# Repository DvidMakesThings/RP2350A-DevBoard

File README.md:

# RP2350A-DevBoard Project

## Contents
This folder contains all the documents related to the RP2350A-DevBoard project.

## Usage
To use the files in this project, navigate to the respective directories and follow the instructions provided in each document.

## License
This project is licensed under the MIT License.

## Contact
For any questions or feedback, please contact:
- Email: [s.dvid@hotmail.com](mailto:s.dvid@hotmail.com)
- GitHub: [DvidMakesThings](https://github.com/DvidMakesThings)

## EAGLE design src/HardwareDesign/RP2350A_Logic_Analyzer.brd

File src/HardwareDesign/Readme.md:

# # RP2350A-DevBoard Project Hardware Design Files

## Contents
This folder contains the hardware design files for the RP2350A-DevBoard project. The main components include:
- Schematic diagrams
- PCB layouts
- Bill of Materials (BOM)
- Gerber files

## Usage
To use these hardware design files:
1. Open the schematic diagrams and PCB layouts using EAGLE software.
2. Review the Bill of Materials for required components.
3. Follow the design files to assemble and test the hardware.
4. Use the Gerber files for PCB manufacturing.

## License
This project is licensed under the MIT License.

## Contact
For any questions or feedback, please contact:
- Email: [s.dvid@hotmail.com](mailto:s.dvid@hotmail.com)
- GitHub: [DvidMakesThings](https://github.com/DvidMakesThings)

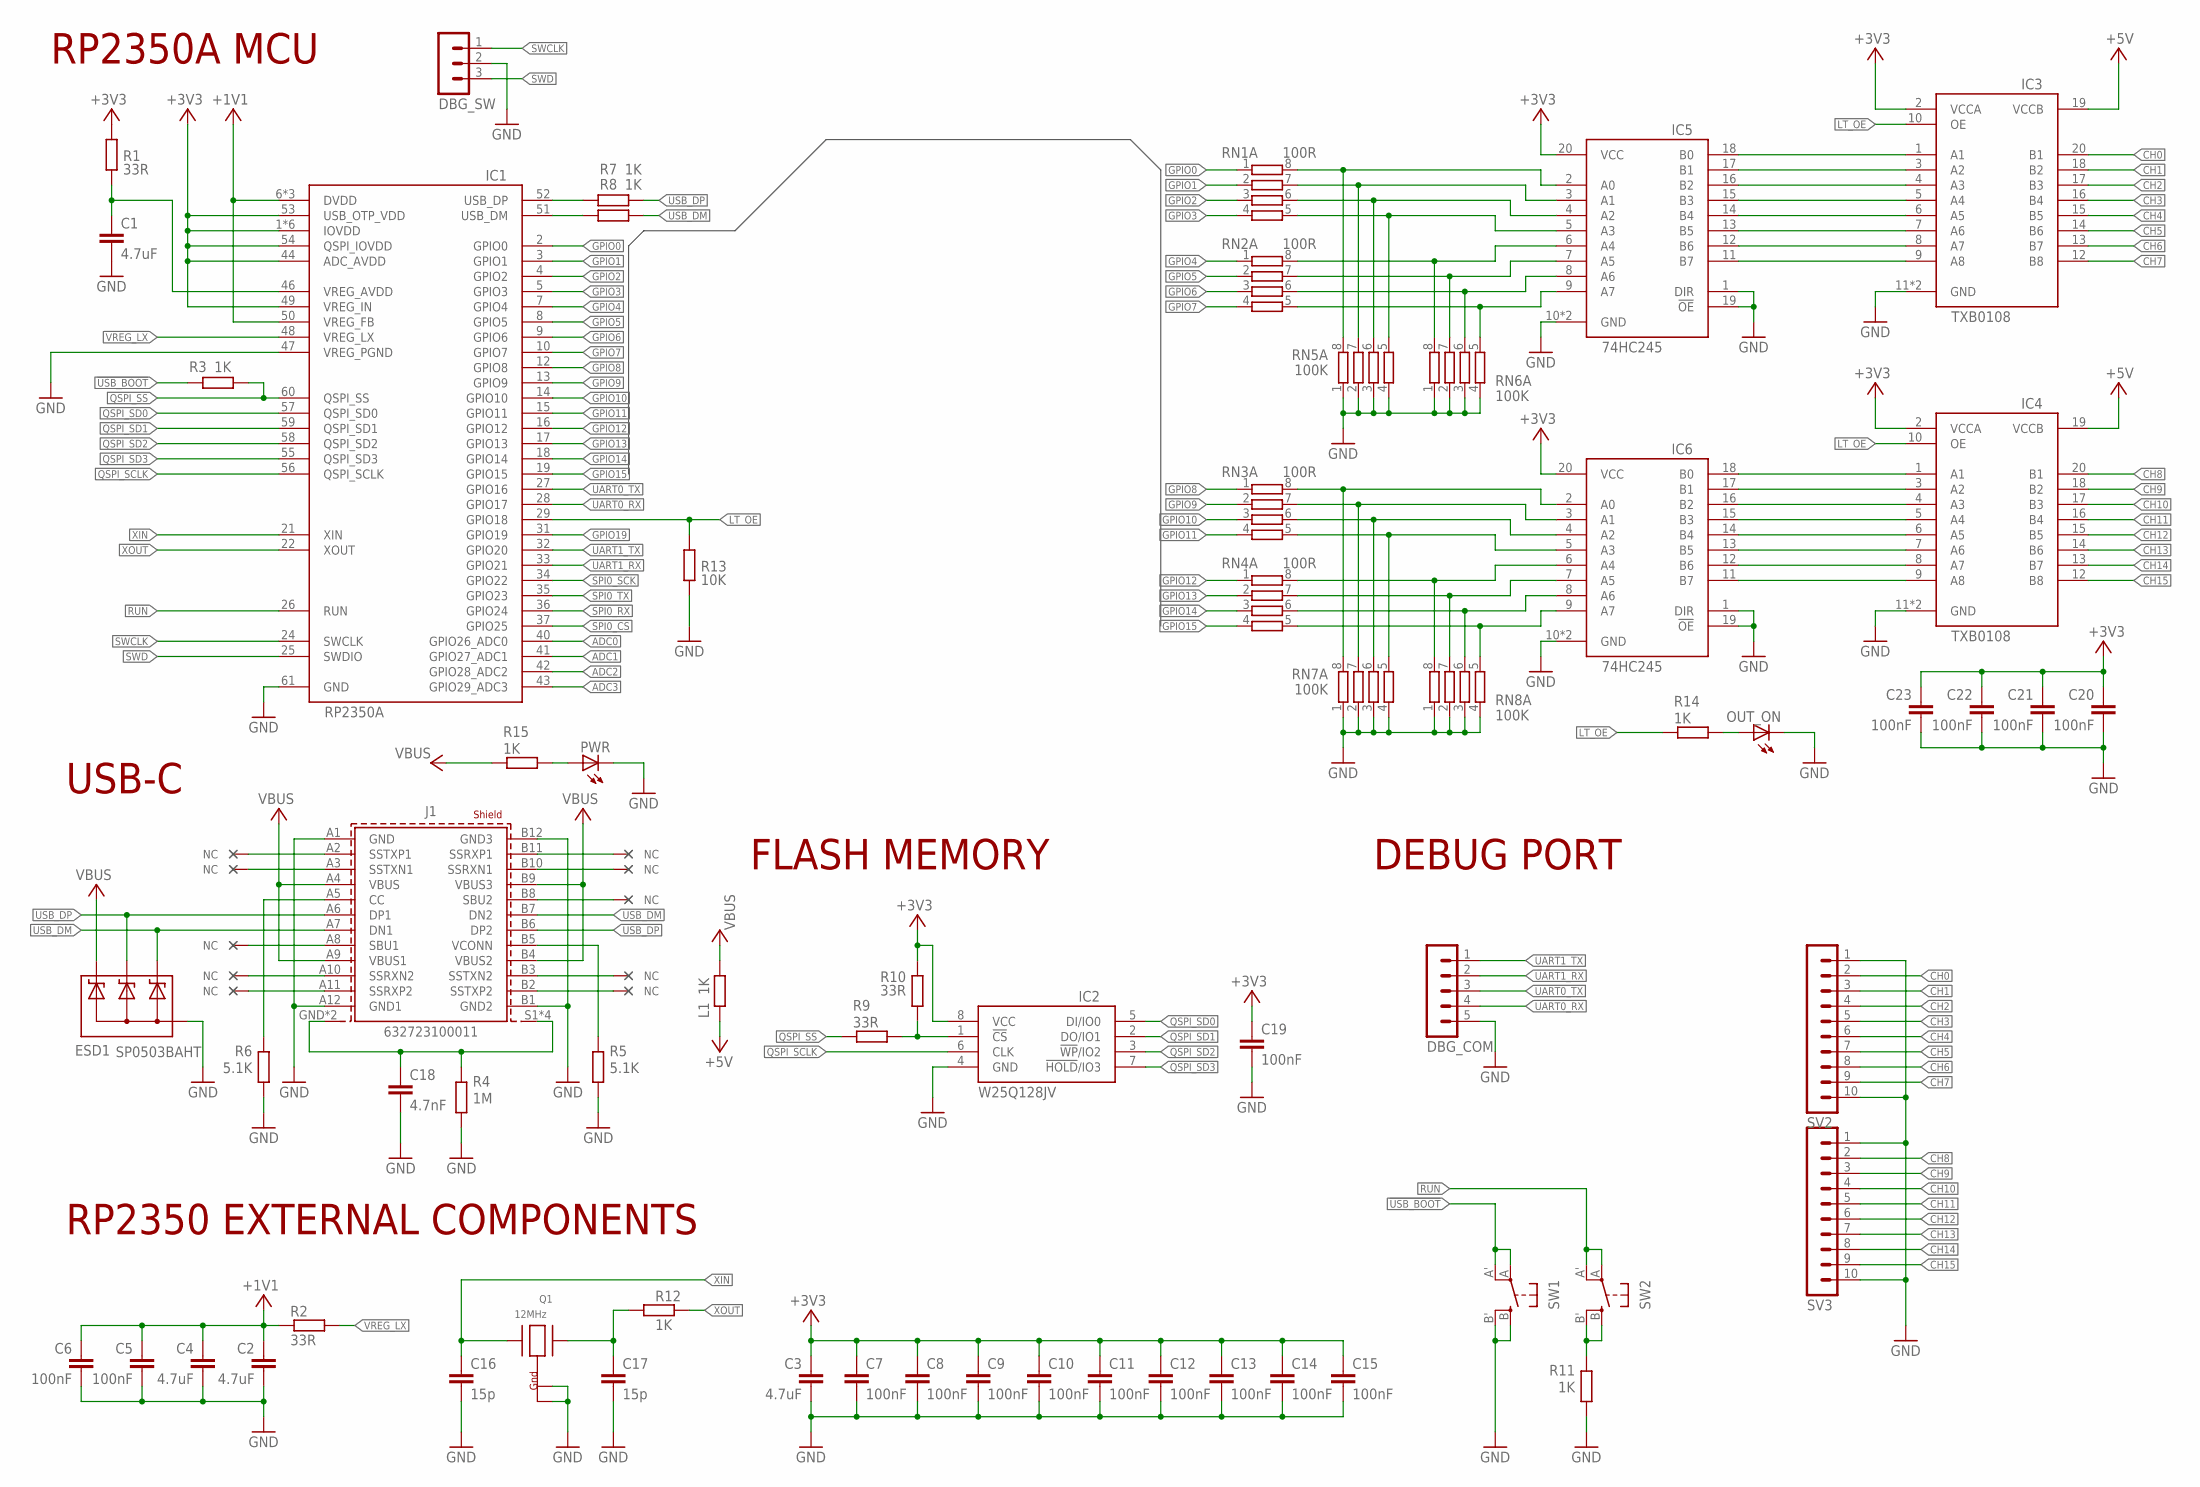
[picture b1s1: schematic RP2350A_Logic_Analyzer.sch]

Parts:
C1, C2, C3, C4: 4.7uF; C0402
C5, C6, C7, C8, C9, C10, C11, C12, C13, C14, C15, C19, C20, C21, C22, C23: 100nF; C0402
C16, C17: 15p; C0402
C18: 4.7nF; C0402
DBG_COM: MA05-1
DBG_SW: MA03-1
ESD1: SP0503BAHT; SOT143
IC1: RP2350AA; QFN40P700X700X85-61T340N
IC2: W25Q128JVP; SON127P600X500X75-8N
IC3, IC4: TXB0108RGY; QFN50P350X450X100-25T200X300N
IC5, IC6: 74HC245BQ; QFN50P250X450X90-21T100X300N
J1: 632723100011
L1: 1K; R0402
OUT_ON: LEDCHIPLED_0603; CHIPLED_0603
PWR: LEDCHIPLED_0603; CHIPLED_0603
Q1: 12MHz; NX3225
R1, R2, R9, R10: 33R; R0402
R3, R7, R8, R11, R12, R14, R15: 1K; R0402
R4: 1M; R0402
R5, R6: 5.1K; R0402
R13: 10K; R0402
RN1, RN2, RN3, RN4: 100R; 0603-ARC
RN5, RN6, RN7, RN8: 100K; 0603-ARC
SV2, SV3: MA10-1
SW1, SW2: SPST_TACT-EVQQ2; EVQ-Q2

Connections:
!USB_BOOT: R3.1, SW1.A, SW1.A' (P1)
+1V1: C2.1, C4.1, C5.1, C6.1, IC1.6 (DVDD), IC1.23 (DVDD), IC1.39 (DVDD), IC1.50 (VREG_FB), R2.2
+3V3: C3.1, C7.1, C8.1, C9.1, C10.1, C11.1, C12.1, C13.1, C14.1, C15.1, C19.1, C20.1, C21.1, C22.1, C23.1, IC1.1 (IOVDD), IC1.11 (IOVDD), IC1.20 (IOVDD), IC1.30 (IOVDD), IC1.38 (IOVDD), IC1.44 (ADC_AVDD), IC1.45 (IOVDD), IC1.49 (VREG_IN), IC1.53 (USB_OTP_VDD), IC1.54 (QSPI_IOVDD), IC2.8 (VCC), IC3.2 (VCCA), IC4.2 (VCCA), IC5.20 (VCC), IC6.20 (VCC), R1.1, R10.1
+5V: IC3.19 (VCCB), IC4.19 (VCCB), L1.1
ADC0: IC1.40 (GPIO26_ADC0)
ADC1: IC1.41 (GPIO27_ADC1)
ADC2: IC1.42 (GPIO28_ADC2)
ADC3: IC1.43 (GPIO29_ADC3)
CH0: IC3.20 (B1), SV2.2
CH1: IC3.18 (B2), SV2.3
CH2: IC3.17 (B3), SV2.4
CH3: IC3.16 (B4), SV2.5
CH4: IC3.15 (B5), SV2.6
CH5: IC3.14 (B6), SV2.7
CH6: IC3.13 (B7), SV2.8
CH7: IC3.12 (B8), SV2.9
CH8: IC4.20 (B1), SV3.2
CH9: IC4.18 (B2), SV3.3
CH10: IC4.17 (B3), SV3.4
CH11: IC4.16 (B4), SV3.5
CH12: IC4.15 (B5), SV3.6
CH13: IC4.14 (B6), SV3.7
CH14: IC4.13 (B7), SV3.8
CH15: IC4.12 (B8), SV3.9
DM: IC1.51 (USB_DM), R8.1
DP: IC1.52 (USB_DP), R7.1
GND: C1.2, C2.2, C3.2, C4.2, C5.2, C6.2, C7.2, C8.2, C9.2, C10.2, C11.2, C12.2, C13.2, C14.2, C15.2, C16.2, C17.2, C18.2, C19.2, C20.2, C21.2, C22.2, C23.2, DBG_COM.5, DBG_SW.2, ESD1.1 (A), IC1.47 (VREG_PGND), IC1.61 (GND), IC2.4 (GND), IC3.11 (GND), IC3.PAD (GND), IC4.11 (GND), IC4.PAD (GND), IC5.1 (DIR), IC5.10 (GND), IC5.19 (!OE), IC5.PAD (GND), IC6.1 (DIR), IC6.10 (GND), IC6.19 (!OE), IC6.PAD (GND), J1.A1 (GND), J1.A12 (GND1), J1.B1 (GND2), J1.B12 (GND3), OUT_ON.C, PWR.C, Q1.2 (G2), Q1.4 (G1), R4.1, R5.1, R6.1, R11.1, R13.2, RN5.1, RN5.2 (1), RN5.3 (1), RN5.4 (1), RN6.1, RN6.2 (1), RN6.3 (1), RN6.4 (1), RN7.1, RN7.2 (1), RN7.3 (1), RN7.4 (1), RN8.1, RN8.2 (1), RN8.3 (1), RN8.4 (1), SV2.1, SV2.10, SV3.1, SV3.10, SW1.B (S), SW1.B' (S1)
GPIO0: IC1.2 (GPIO0), RN1.1
GPIO1: IC1.3 (GPIO1), RN1.2 (1)
GPIO2: IC1.4 (GPIO2), RN1.3 (1)
GPIO3: IC1.5 (GPIO3), RN1.4 (1)
GPIO4: IC1.7 (GPIO4), RN2.1
GPIO5: IC1.8 (GPIO5), RN2.2 (1)
GPIO6: IC1.9 (GPIO6), RN2.3 (1)
GPIO7: IC1.10 (GPIO7), RN2.4 (1)
GPIO8: IC1.12 (GPIO8), RN3.1
GPIO9: IC1.13 (GPIO9), RN3.2 (1)
GPIO10: IC1.14 (GPIO10), RN3.3 (1)
GPIO11: IC1.15 (GPIO11), RN3.4 (1)
GPIO12: IC1.16 (GPIO12), RN4.1
GPIO13: IC1.17 (GPIO13), RN4.2 (1)
GPIO14: IC1.18 (GPIO14), RN4.3 (1)
GPIO15: IC1.19 (GPIO15), RN4.4 (1)
GPIO19: IC1.31 (GPIO19)
LT_OE: IC1.29 (GPIO18), IC3.10 (OE), IC4.10 (OE), R13.1, R14.1
unnamed: C1.1, IC1.46 (VREG_AVDD), R1.2
unnamed: R11.2, SW2.B (S), SW2.B' (S1)
unnamed: IC4.1 (A1), IC6.18 (B0)
unnamed: J1.A5 (CC), R6.2
unnamed: J1.B5 (VCONN), R5.2
unnamed: C18.1, J1.GND (SHIELD), J1.GND1 (SHIELD), J1.S1 (SHIELD1), J1.S2 (SHIELD1), J1.S3 (SHIELD1), J1.S4 (SHIELD1), R4.2
unnamed: IC4.3 (A2), IC6.17 (B1)
unnamed: IC4.4 (A3), IC6.16 (B2)
unnamed: IC2.1 (!CS), R9.2, R10.2
unnamed: IC4.5 (A4), IC6.15 (B3)
unnamed: IC4.6 (A5), IC6.14 (B4)
unnamed: IC4.7 (A6), IC6.13 (B5)
unnamed: IC4.8 (A7), IC6.12 (B6)
unnamed: IC4.9 (A8), IC6.11 (B7)
unnamed: IC3.1 (A1), IC5.18 (B0)
unnamed: IC3.3 (A2), IC5.17 (B1)
unnamed: IC3.4 (A3), IC5.16 (B2)
unnamed: IC3.5 (A4), IC5.15 (B3)
unnamed: IC3.6 (A5), IC5.14 (B4)
unnamed: IC3.7 (A6), IC5.13 (B5)
unnamed: IC3.8 (A7), IC5.12 (B6)
unnamed: IC3.9 (A8), IC5.11 (B7)
unnamed: IC5.2 (A0), RN1.8 (2), RN5.8 (2)
unnamed: IC5.3 (A1), RN1.7 (2), RN5.7 (2)
unnamed: IC5.4 (A2), RN1.6 (2), RN5.6 (2)
unnamed: IC5.5 (A3), RN1.5 (2), RN5.5 (2)
unnamed: IC5.6 (A4), RN2.8 (2), RN6.8 (2)
unnamed: IC5.7 (A5), RN2.7 (2), RN6.7 (2)
unnamed: IC5.8 (A6), RN2.6 (2), RN6.6 (2)
unnamed: IC5.9 (A7), RN2.5 (2), RN6.5 (2)
unnamed: IC6.2 (A0), RN3.8 (2), RN7.8 (2)
unnamed: IC6.3 (A1), RN3.7 (2), RN7.7 (2)
unnamed: IC6.4 (A2), RN3.6 (2), RN7.6 (2)
unnamed: IC6.5 (A3), RN3.5 (2), RN7.5 (2)
unnamed: IC6.6 (A4), RN4.8 (2), RN8.8 (2)
unnamed: IC6.7 (A5), RN4.7 (2), RN8.7 (2)
unnamed: IC6.8 (A6), RN4.6 (2), RN8.6 (2)
unnamed: IC6.9 (A7), RN4.5 (2), RN8.5 (2)
unnamed: OUT_ON.A, R14.2
unnamed: PWR.A, R15.2
OU: C17.1, Q1.1 (X1), R12.1
QSPI_SCLK: IC1.56 (QSPI_SCLK), IC2.6 (CLK)
QSPI_SD0: IC1.57 (QSPI_SD0), IC2.5 (DI/IO0)
QSPI_SD1: IC1.59 (QSPI_SD1), IC2.2 (DO/IO1)
QSPI_SD2: IC1.58 (QSPI_SD2), IC2.3 (!WP!/IO2)
QSPI_SD3: IC1.55 (QSPI_SD3), IC2.7 (!HOLD!/IO3)
QSPI_SS: IC1.60 (QSPI_SS), R3.2, R9.1
RUN: IC1.26 (RUN), SW2.A, SW2.A' (P1)
SPI0_CS: IC1.37 (GPIO25)
SPI0_RX: IC1.36 (GPIO24)
SPI0_SCK: IC1.34 (GPIO22)
SPI0_TX: IC1.35 (GPIO23)
SWCLK: DBG_SW.1, IC1.24 (SWCLK)
SWD: DBG_SW.3, IC1.25 (SWDIO)
UART0_RX: DBG_COM.4, IC1.28 (GPIO17)
UART0_TX: DBG_COM.3, IC1.27 (GPIO16)
UART1_RX: DBG_COM.2, IC1.33 (GPIO21)
UART1_TX: DBG_COM.1, IC1.32 (GPIO20)
USB_DM: ESD1.2 (C1), J1.A7 (DN1), J1.B7 (DN2), R8.2
USB_DP: ESD1.3 (C2), J1.A6 (DP1), J1.B6 (DP2), R7.2
VBUS: ESD1.4 (C3), J1.A4 (VBUS), J1.A9 (VBUS1), J1.B4 (VBUS2), J1.B9 (VBUS3), L1.2, R15.1
VREG_LX: IC1.48 (VREG_LX), R2.1
XIN: C16.1, IC1.21 (XIN), Q1.3 (X2)
XOUT: IC1.22 (XOUT), R12.2

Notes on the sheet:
RP2350A MCU
USB-C
FLASH MEMORY
RP2350 EXTERNAL COMPONENTS
DEBUG PORT

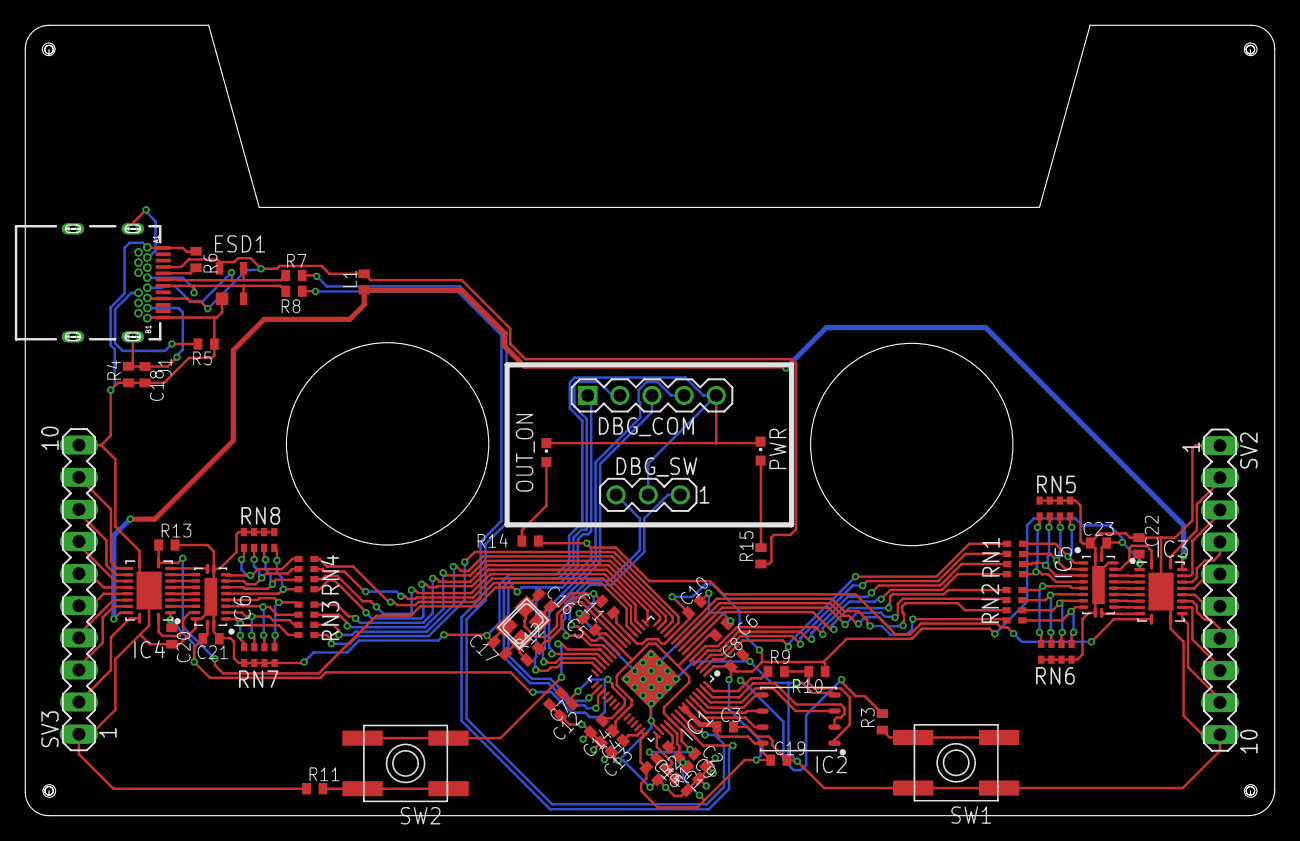
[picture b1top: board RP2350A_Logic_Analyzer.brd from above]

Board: 2 copper layers, 98.7 x 62.4 mm, 64 parts (0 on the bottom side), 100 nets.

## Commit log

2024-11-24 initial creation

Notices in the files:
parts and their libraries:
Eagle_WR-USB: Copyright: Würth Elektronik
